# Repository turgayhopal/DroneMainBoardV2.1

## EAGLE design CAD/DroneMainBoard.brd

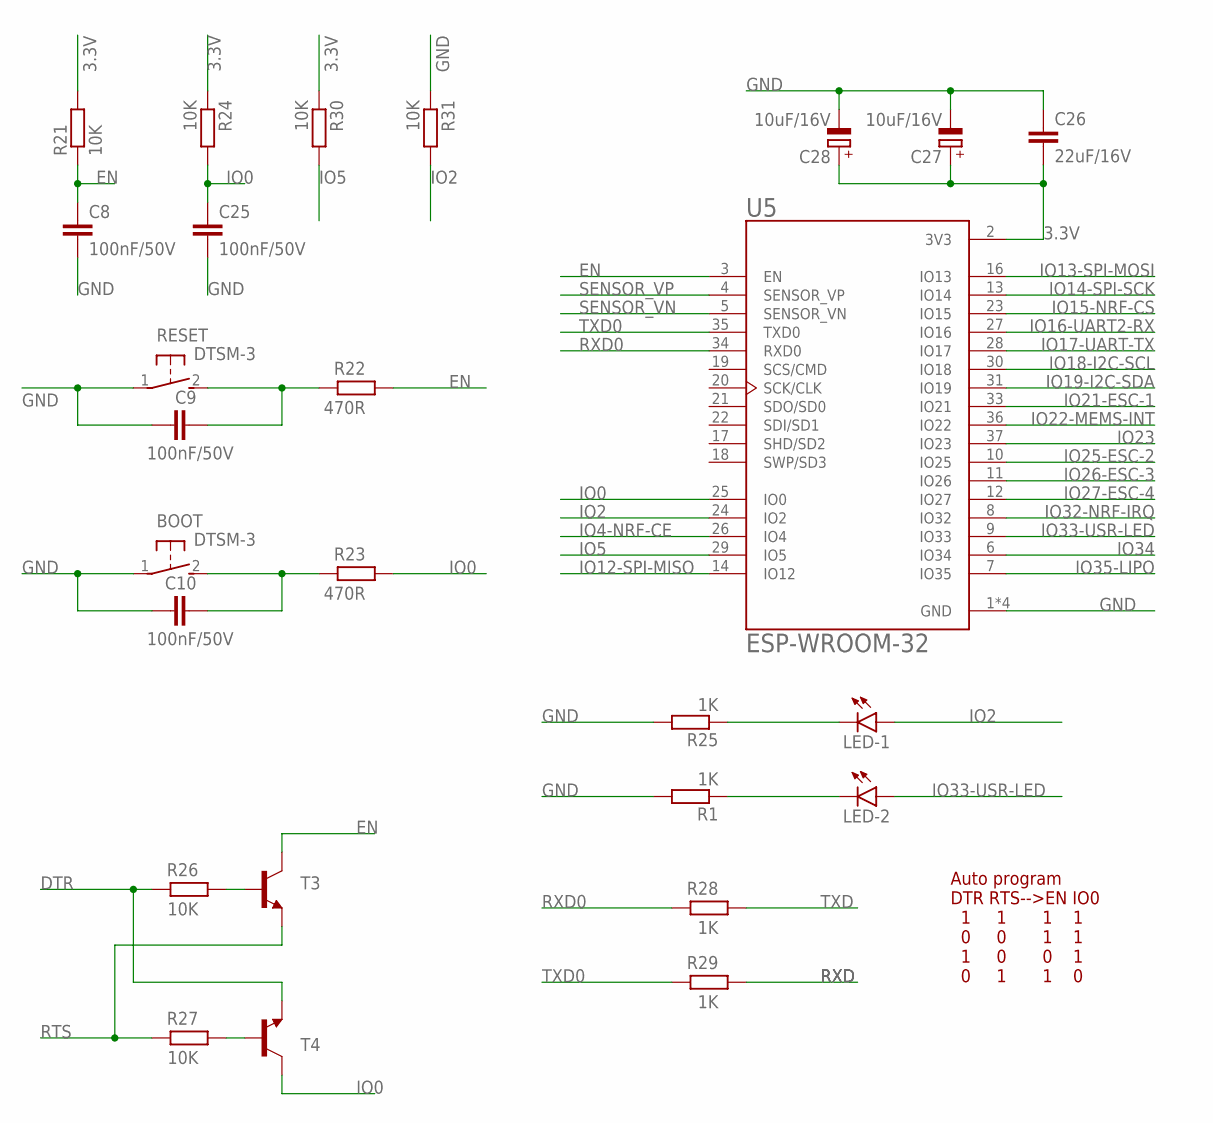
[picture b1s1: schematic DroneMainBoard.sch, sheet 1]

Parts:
BOOT: DTSM-3
C8, C9, C10, C25: 100nF/50V; C0805
C26: 22uF/16V; C0805
C27, C28: 10uF/16V; SMC_A
LED-1, LED-2: LEDCHIP-LED0805; CHIP-LED0805
R1, R25, R28, R29: 1K; R0805
R21, R24, R26, R27, R30, R31: 10K; R0805
R22, R23: 470R; R0805
RESET: DTSM-3
T3, T4: -NPN-SOT23-EBC; SOT23-EBC
U5: ESP-WROOM-32; MODULE_ESP-WROOM-32

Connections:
3.3V: C26.2, C27.+, C28.+, R21.2, R24.1, R30.1, U5.2 (3V3); also elsewhere on the board
DTR: R26.2, T4.E; also elsewhere on the board
EN: C8.1, R21.1, R22.1, T3.C, U5.3 (EN)
GND: BOOT.1, C8.2, C9.1, C10.1, C25.2, C26.1, C27.-, C28.-, R1.2, R25.2, R31.1, RESET.1, U5.1 (GND), U5.1.1 (GND), U5.15 (GND), U5.38 (GND); also elsewhere on the board
IO0: C25.1, R23.1, R24.2, T4.C, U5.25 (IO0)
IO2: LED-1.A, R31.2, U5.24 (IO2)
IO4-NRF-CE: U5.26 (IO4); also elsewhere on the board
IO5: R30.2, U5.29 (IO5)
IO12-SPI-MISO: U5.14 (IO12); also elsewhere on the board
IO13-SPI-MOSI: U5.16 (IO13); also elsewhere on the board
IO14-SPI-SCK: U5.13 (IO14); also elsewhere on the board
IO15-NRF-CS: U5.23 (IO15); also elsewhere on the board
IO16-UART2-RX: U5.27 (IO16)
IO17-UART-TX: U5.28 (IO17)
IO18-I2C-SCL: U5.30 (IO18); also elsewhere on the board
IO19-I2C-SDA: U5.31 (IO19); also elsewhere on the board
IO21-ESC-1: U5.33 (IO21); also elsewhere on the board
IO22-MEMS-INT: U5.36 (IO22); also elsewhere on the board
IO23: U5.37 (IO23)
IO25-ESC-2: U5.10 (IO25); also elsewhere on the board
IO26-ESC-3: U5.11 (IO26); also elsewhere on the board
IO27-ESC-4: U5.12 (IO27); also elsewhere on the board
IO32-NRF-IRQ: U5.8 (IO32); also elsewhere on the board
IO33-USR-LED: LED-2.A, U5.9 (IO33)
IO34: U5.6 (IO34)
IO35-LIPO: U5.7 (IO35); also elsewhere on the board
unnamed: LED-2.C, R1.1
unnamed: BOOT.2, C10.2, R23.2
unnamed: R26.1, T3.B
unnamed: R27.1, T4.B
unnamed: LED-1.C, R25.1
unnamed: C9.2, R22.2, RESET.2
RTS: R27.2, T3.E; also elsewhere on the board
RXD: R29.1; also elsewhere on the board
RXD0: R28.2, U5.34 (RXD0)
SENSOR_VN: U5.5 (SENSOR_VN)
SENSOR_VP: U5.4 (SENSOR_VP)
TXD: R28.1; also elsewhere on the board
TXD0: R29.2, U5.35 (TXD0)

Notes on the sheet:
Auto program DTR RTS-->EN IO0 1 1 1 1 0 0 1 1 1 0 0 1 0 1 1 0

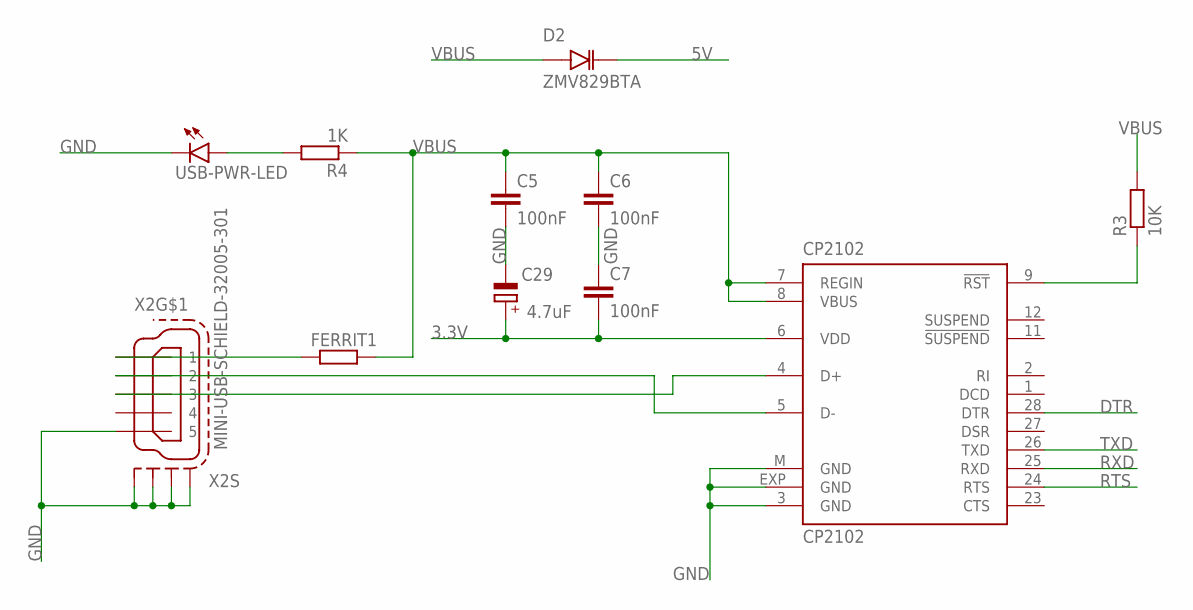
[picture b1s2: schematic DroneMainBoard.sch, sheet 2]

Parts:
C5, C6, C7: 100nF; C0805
C29: 4.7uF; SMC_A
CP2102: CP2102; MLP28
D2: ZMV829BTA; SOD2512X116N
FERRIT1: R-EU_R0805; R0805
R3: 10K; R0805
R4: 1K; R0805
USB-PWR-LED: LEDCHIPLED_0805; CHIPLED_0805
X2: MINI-USB-SCHIELD-32005-301; 32005-301

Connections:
3.3V: C7.2, C29.+, CP2102.6 (VDD); also elsewhere on the board
5V: D2.K; also elsewhere on the board
DTR: CP2102.28 (DTR); also elsewhere on the board
GND: C5.2, C6.2, C7.1, C29.-, CP2102.3 (GND), CP2102.EXP (GND), CP2102.M (GND), USB-PWR-LED.C, X2.5, X2.M1 (S1), X2.M2 (S2), X2.M3 (S3), X2.M4 (S4); also elsewhere on the board
unnamed: CP2102.9 (!RST), R3.1
unnamed: FERRIT1.1, X2.1
unnamed: CP2102.5 (D-), X2.2
unnamed: CP2102.4 (D+), X2.3
unnamed: R4.2, USB-PWR-LED.A
RTS: CP2102.24 (RTS); also elsewhere on the board
RXD: CP2102.25 (RXD); also elsewhere on the board
TXD: CP2102.26 (TXD); also elsewhere on the board
VBUS: C5.1, C6.1, CP2102.7 (REGIN), CP2102.8 (VBUS), D2.A, FERRIT1.2, R3.2, R4.1

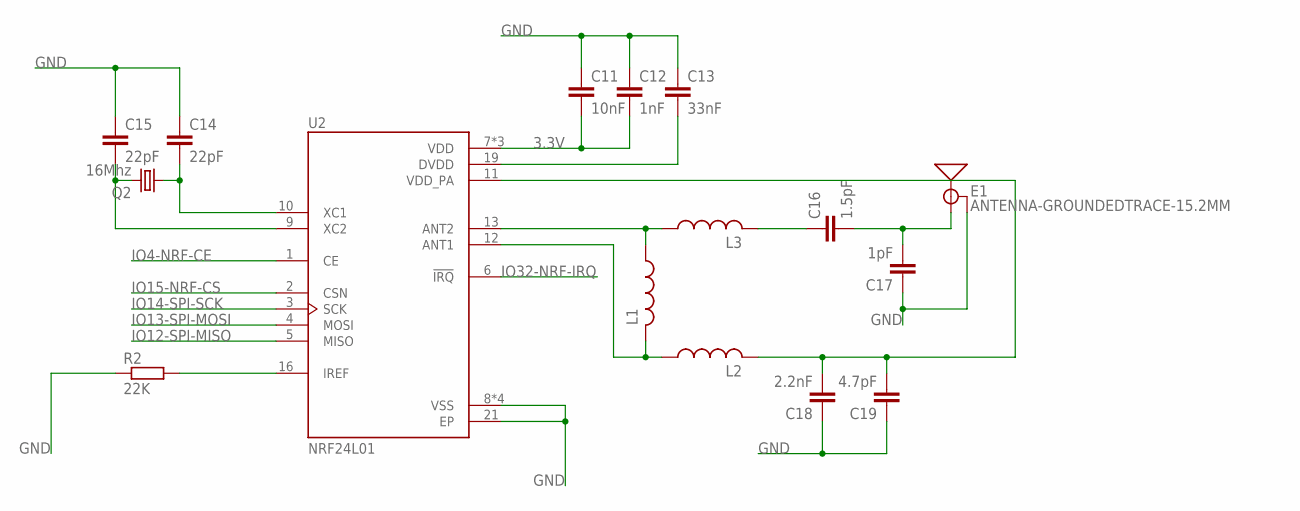
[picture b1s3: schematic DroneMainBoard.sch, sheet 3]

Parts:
C11: 10nF; C0805
C12: 1nF; C0805
C13: 33nF; C0805
C14, C15: 22pF; C0805
C16: 1.5pF; C0805
C17: 1pF; C0805
C18: 2.2nF; C0805
C19: 4.7pF; C0805
E1: ANTENNA-GROUNDEDTRACE-15.2MM; TRACE_ANTENNA_2.4GHZ_15.2MM
L1, L2, L3: L-USL2012C; L2012C
Q2: 16Mhz; HC49/S
R2: 22K; R0805
U2: NRF24L01; QFN50P400X400X95-21N

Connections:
3.3V: C11.2, C12.2, U2.7 (VDD), U2.15 (VDD), U2.18 (VDD); also elsewhere on the board
GND: C11.1, C12.1, C13.1, C14.1, C15.1, C17.1, C18.1, C19.1, E1.GND, R2.1, U2.8 (VSS), U2.14 (VSS), U2.17 (VSS), U2.20 (VSS), U2.21 (EP); also elsewhere on the board
IO4-NRF-CE: U2.1 (CE); also elsewhere on the board
IO12-SPI-MISO: U2.5 (MISO); also elsewhere on the board
IO13-SPI-MOSI: U2.4 (MOSI); also elsewhere on the board
IO14-SPI-SCK: U2.3 (SCK); also elsewhere on the board
IO15-NRF-CS: U2.2 (CSN); also elsewhere on the board
IO32-NRF-IRQ: U2.6 (!IRQ); also elsewhere on the board
unnamed: C14.2, Q2.1, U2.10 (XC1)
unnamed: C15.2, Q2.2, U2.9 (XC2)
unnamed: C16.2, C17.2, E1.ANT (SIGNAL)
unnamed: R2.2, U2.16 (IREF)
unnamed: C13.2, U2.19 (DVDD)
unnamed: C18.2, C19.2, L2.2, U2.11 (VDD_PA)
unnamed: L1.1, L3.1, U2.13 (ANT2)
unnamed: L1.2, L2.1, U2.12 (ANT1)
unnamed: C16.1, L3.2

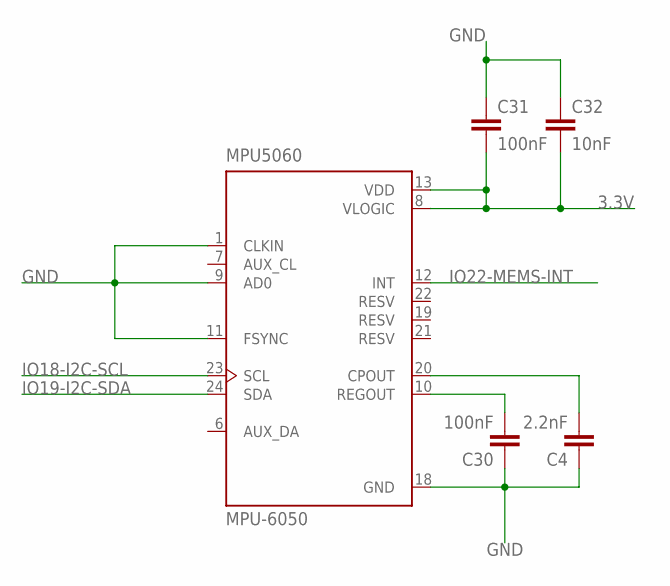
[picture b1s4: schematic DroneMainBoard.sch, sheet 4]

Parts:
C4: 2.2nF; C0805
C30, C31: 100nF; C0805
C32: 10nF; C0805
MPU5060: MPU-6050; QFN50P400X400X95-24N

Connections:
3.3V: C31.2, C32.2, MPU5060.8 (VLOGIC), MPU5060.13 (VDD); also elsewhere on the board
GND: C4.1, C30.1, C31.1, C32.1, MPU5060.1 (CLKIN), MPU5060.9 (AD0), MPU5060.11 (FSYNC), MPU5060.18 (GND); also elsewhere on the board
IO18-I2C-SCL: MPU5060.23 (SCL); also elsewhere on the board
IO19-I2C-SDA: MPU5060.24 (SDA); also elsewhere on the board
IO22-MEMS-INT: MPU5060.12 (INT); also elsewhere on the board
unnamed: C30.2, MPU5060.10 (REGOUT)
unnamed: C4.2, MPU5060.20 (CPOUT)

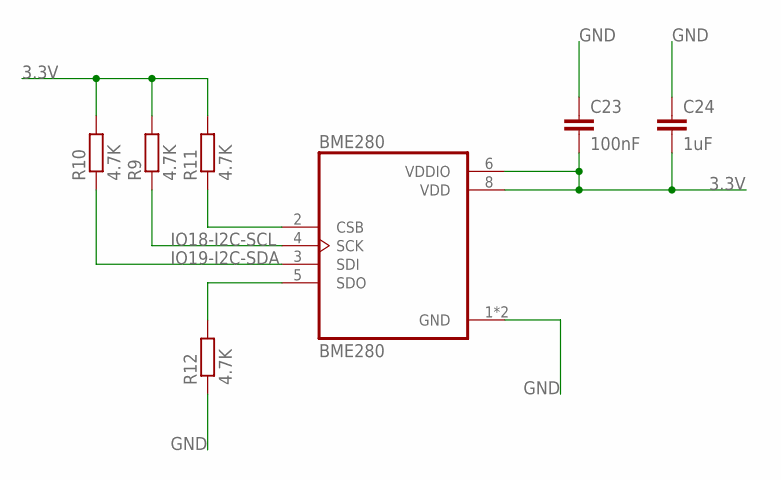
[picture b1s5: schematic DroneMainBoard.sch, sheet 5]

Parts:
BME280: BME280; PSON65P250X250X100-8N
C23: 100nF; C0805
C24: 1uF; C0805
R9, R10, R11, R12: 4.7K; R0805

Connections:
3.3V: BME280.6 (VDDIO), BME280.8 (VDD), C23.2, C24.2, R9.2, R10.2, R11.2; also elsewhere on the board
GND: BME280.1 (GND), BME280.7 (GND), C23.1, C24.1, R12.1; also elsewhere on the board
IO18-I2C-SCL: BME280.4 (SCK), R9.1; also elsewhere on the board
IO19-I2C-SDA: BME280.3 (SDI), R10.1; also elsewhere on the board
unnamed: BME280.2 (CSB), R11.1
unnamed: BME280.5 (SDO), R12.2

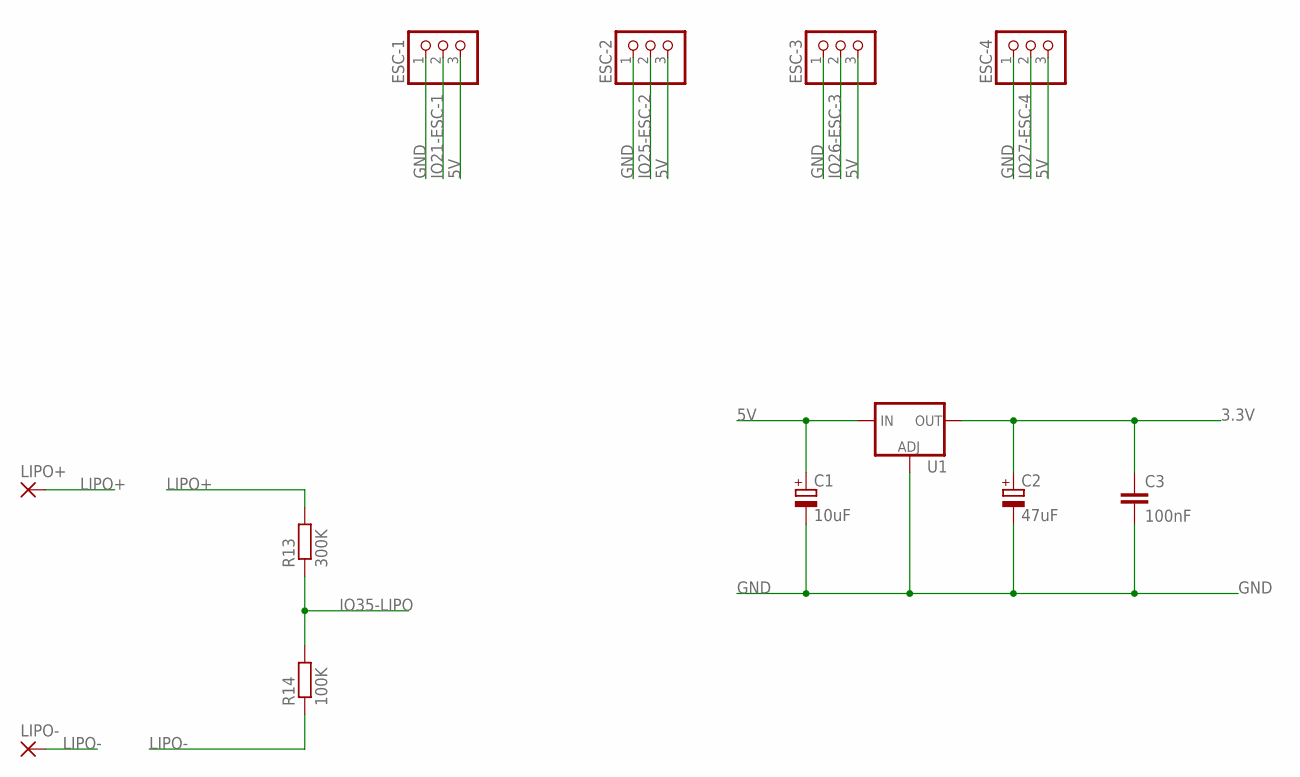
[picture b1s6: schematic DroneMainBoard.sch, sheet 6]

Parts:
C1: 10uF; SMC_A
C2: 47uF; SMC_A
C3: 100nF; C0805
ESC-1, ESC-2, ESC-3, ESC-4: PINHD-1X3; 1X03
LIPO+: 2,15/1,0
LIPO-: 2,15/1,0
R13: 300K; R0805
R14: 100K; R0805
U1: V_REG_LM1117SOT223; SOT223

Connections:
3.3V: C2.+, C3.1, U1.2 (OUT), U1.4 (OUT); also elsewhere on the board
5V: C1.+, ESC-1.3, ESC-2.3, ESC-3.3, ESC-4.3, U1.3 (IN); also elsewhere on the board
GND: C1.-, C2.-, C3.2, ESC-1.1, ESC-2.1, ESC-3.1, ESC-4.1, U1.1 (ADJ); also elsewhere on the board
IO21-ESC-1: ESC-1.2; also elsewhere on the board
IO25-ESC-2: ESC-2.2; also elsewhere on the board
IO26-ESC-3: ESC-3.2; also elsewhere on the board
IO27-ESC-4: ESC-4.2; also elsewhere on the board
IO35-LIPO: R13.1, R14.2; also elsewhere on the board
LIPO+: LIPO+.1, R13.2
LIPO-: LIPO-.1, R14.1

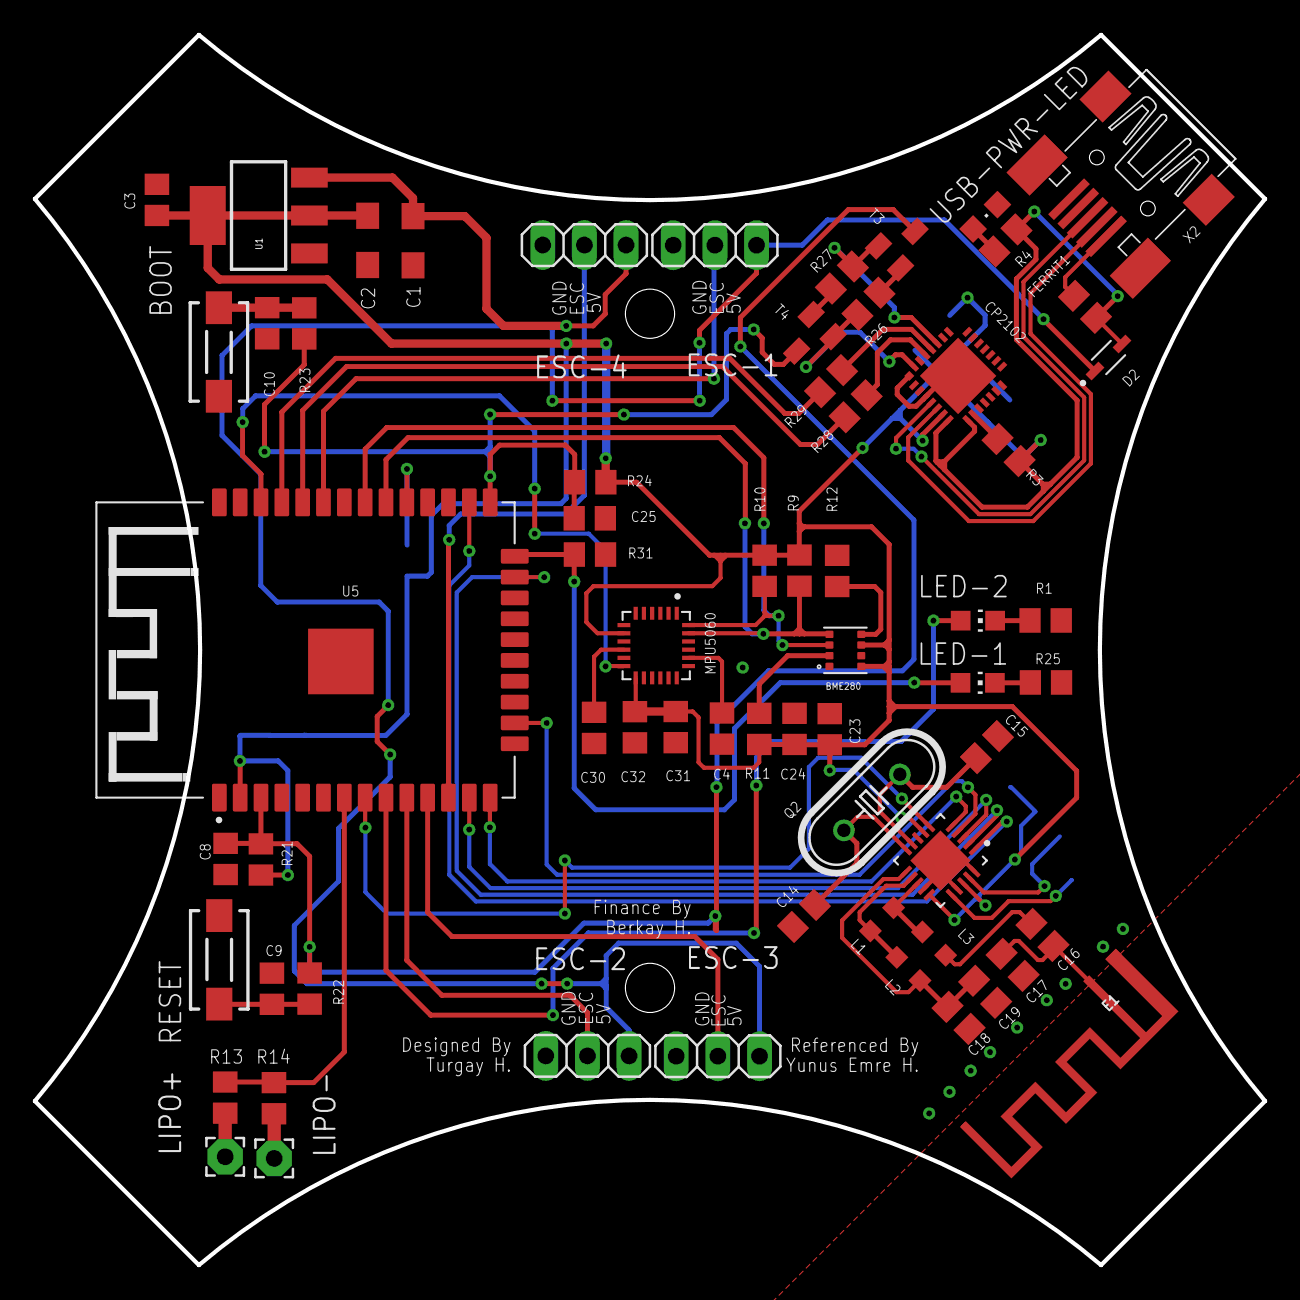
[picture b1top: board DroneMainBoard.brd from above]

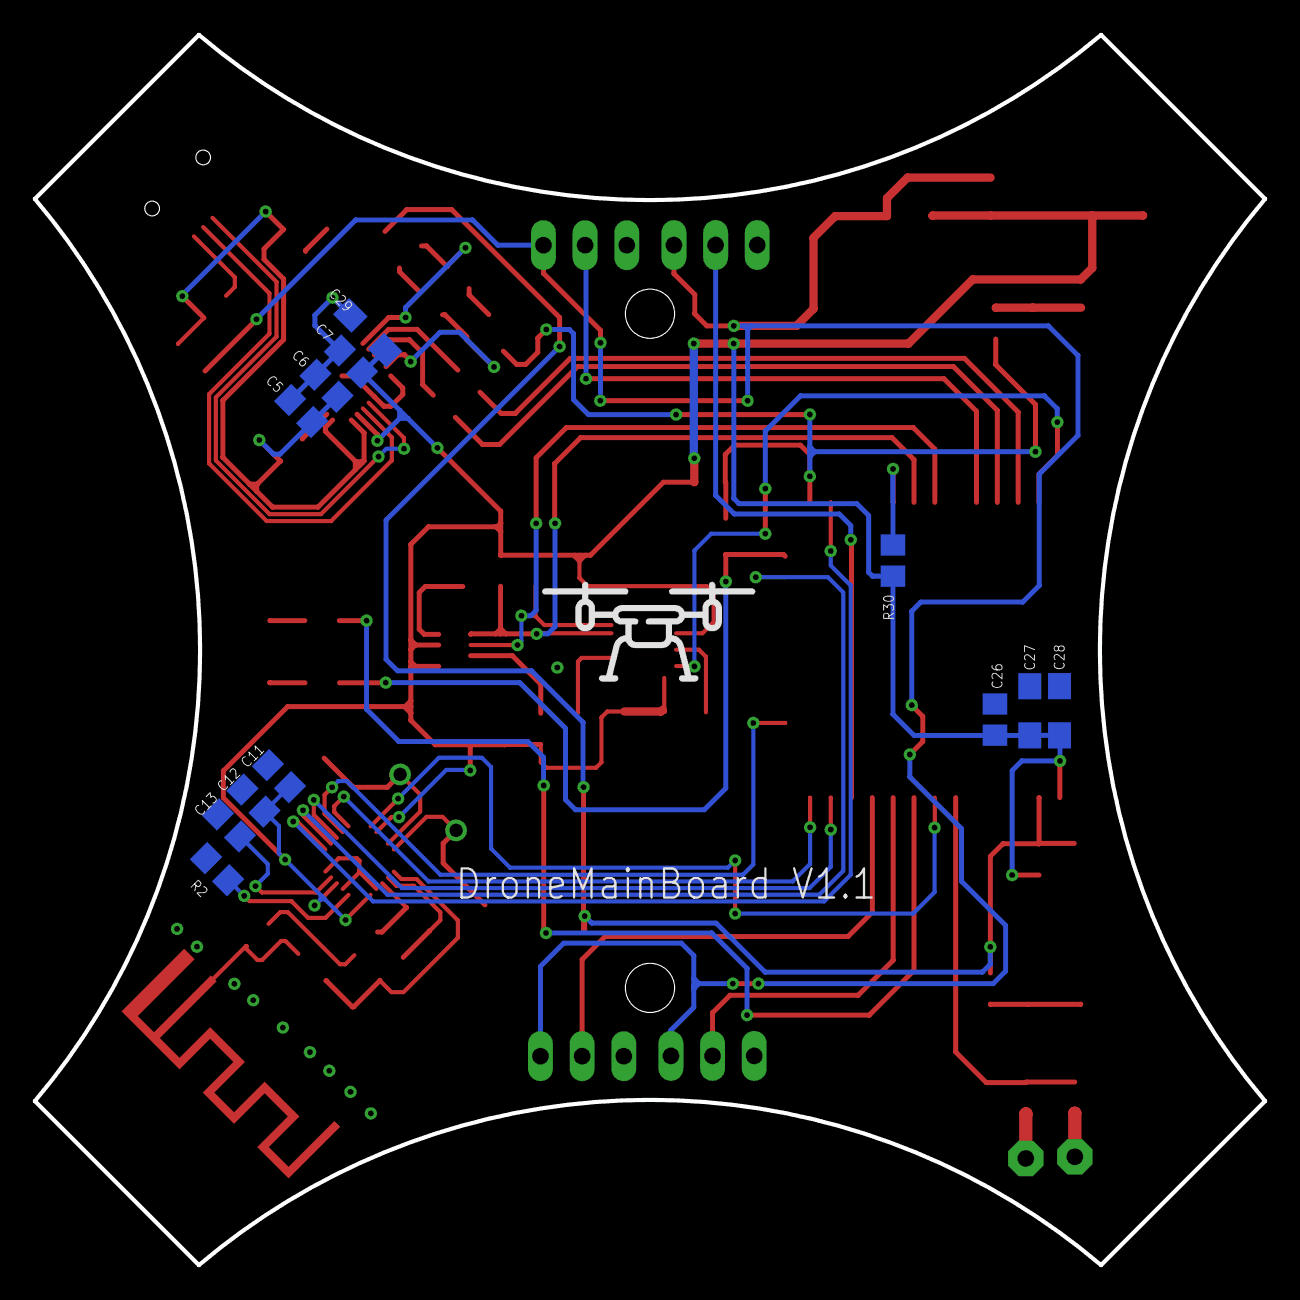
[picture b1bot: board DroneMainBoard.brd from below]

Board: 2 copper layers, 75.0 x 75.0 mm, 77 parts (12 on the bottom side), 55 nets.

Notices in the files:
parts and their libraries:
SparkFun-IC-Power: Licensing: Creative Commons ShareAlike 4.0 International - https://creativecommons.org/licenses/by-sa/4.0
